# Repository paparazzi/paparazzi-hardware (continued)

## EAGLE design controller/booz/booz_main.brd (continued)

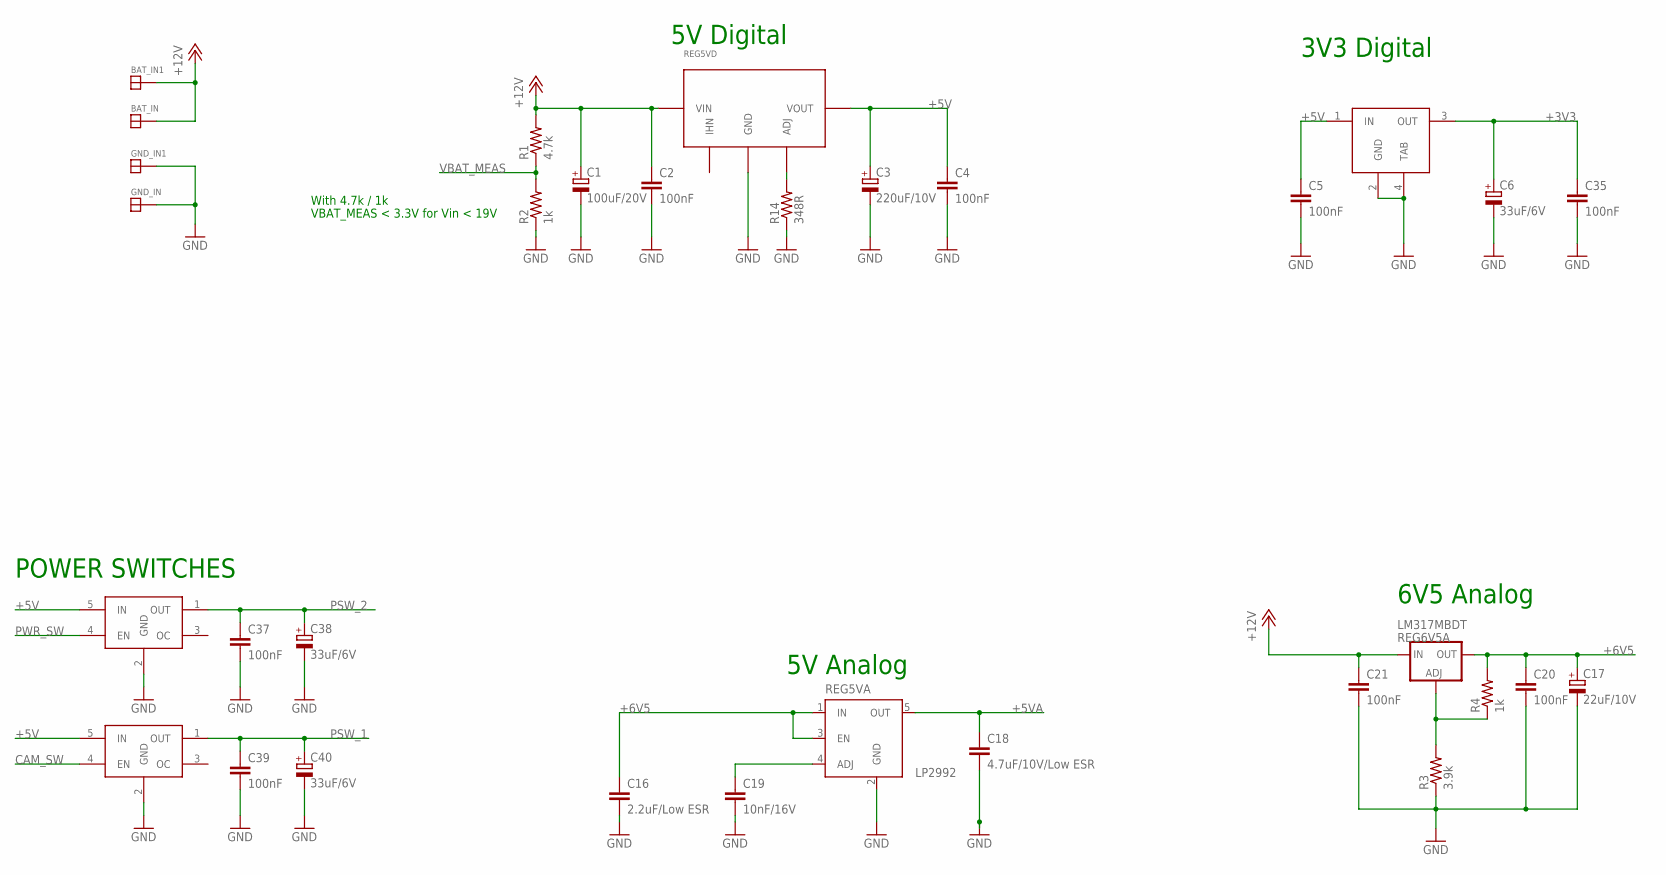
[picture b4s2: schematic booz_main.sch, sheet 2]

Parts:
BAT_IN, BAT_IN1: SOLDER_PAD150_75; SOLD_PAD_150_75
C1: 100uF/20V; SMC_D
C2, C4, C5, C20, C21, C35, C37, C39: 100nF; C0603
C3: 220uF/10V; SMC_D
C6, C38, C40: 33uF/6V; CT3216
C16: 2.2uF/Low ESR; C0603
C17: 22uF/10V; CT3216
C18: 4.7uF/10V/Low ESR; C0805K
C19: 10nF/16V; C0603K
GND_IN, GND_IN1: SOLDER_PAD150_75; SOLD_PAD_150_75
R1: 4.7k; R0603
R2, R4: 1k; R0603
R3: 3.9k; R0603
R14: 348R; R0603
REG3V3D: LM3940IMP-3.3; SOT223-R
REG5VA: LP2992; SOT23-5
REG5VD: PTHTH; PTH_TH
REG6V5A: LM317MBDT; DPACK
U$12, U$13: TPS2051B; SOT23-5L

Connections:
+3V3: C6.+, C35.1, REG3V3D.3 (OUT); also elsewhere on the board
+5V: C3.+, C4.1, C5.1, REG3V3D.1 (IN), REG5VD.P$3 (VOUT), U$12.5 (IN), U$13.5 (IN); also elsewhere on the board
+5VA: C18.1, REG5VA.5 (OUT); also elsewhere on the board
+6V5: C16.1, C17.+, C20.1, R4.2, REG5VA.1 (IN), REG5VA.3 (EN), REG6V5A.4 (OUT); also elsewhere on the board
+12V: BAT_IN.P$1, BAT_IN1.P$1, C1.+, C2.1, C21.1, R1.2, REG5VD.P$1 (VIN), REG6V5A.3 (IN)
CAM_SW: U$13.4 (EN); also elsewhere on the board
GND: C1.-, C2.2, C3.-, C4.2, C5.2, C6.-, C16.2, C17.-, C18.2, C19.2, C20.2, C21.2, C35.2, C37.2, C38.-, C39.2, C40.-, GND_IN.P$1, GND_IN1.P$1, R2.1, R3.1, R14.1, REG3V3D.2 (GND), REG3V3D.4 (TAB), REG5VA.2 (GND), REG5VD.P$2 (GND), U$12.2 (GND), U$13.2 (GND); also elsewhere on the board
unnamed: R14.2, REG5VD.P$4 (ADJ)
unnamed: C19.1, REG5VA.4 (ADJ)
unnamed: R3.2, R4.1, REG6V5A.1 (ADJ)
PSW_1: C39.1, C40.+, U$13.1 (OUT); also elsewhere on the board
PSW_2: C37.1, C38.+, U$12.1 (OUT); also elsewhere on the board
PWR_SW: U$12.4 (EN); also elsewhere on the board
VBAT_MEAS: R1.1, R2.2; also elsewhere on the board

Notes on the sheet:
5V Digital
3V3 Digital
6V5 Analog
5V Analog
POWER SWITCHES
With 4.7k / 1k
VBAT_MEAS < 3.3V for Vin < 19V

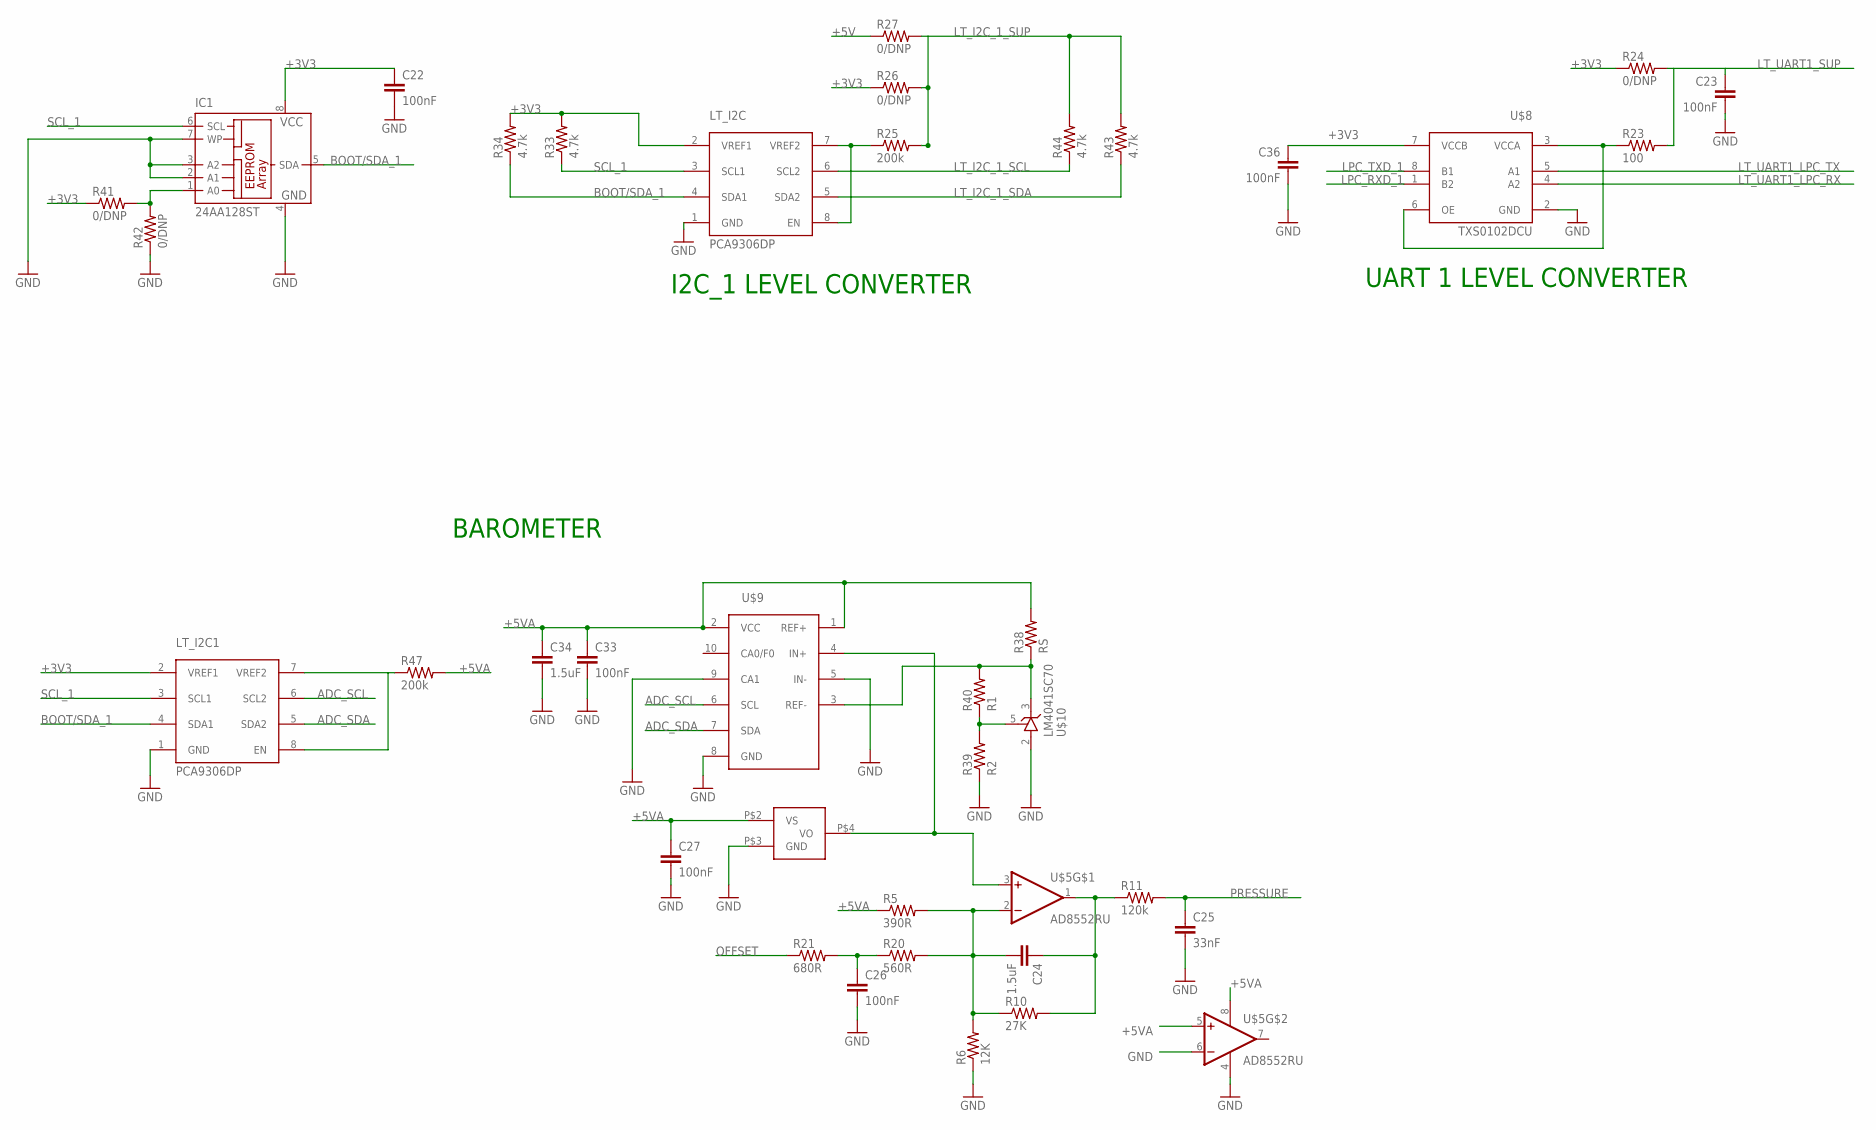
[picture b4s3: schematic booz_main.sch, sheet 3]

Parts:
C22, C23, C26, C27, C33, C36: 100nF; C0603
C24, C34: 1.5uF; C0805
C25: 33nF; C0805K
IC1: 24AA128ST; TSSOP8
LT_I2C, LT_I2C1: PCA9306DP; TSSOP_B3
R5: 390R; R0603
R6: 12K; R0603
R10: 27K; R0603
R11: 120k; R0603
R20: 560R; R0603
R21: 680R; R0603
R23: 100; R0603
R24, R26, R27, R41, R42: 0/DNP; R0603
R25, R47: 200k; R0603
R33, R34, R43, R44: 4.7k; R0603
R38: RS; R0603
R39: R2; R0603
R40: R1; R0603
U$2: MPX6115; CASE_1317
U$5: AD8552RU; TSSOP8
U$8: TXS0102DCU; US8
U$9: LTC2485; DFN10
U$10: LM4041SC70; SC70-5L

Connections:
+3V3: C22.1, C36.1, IC1.8 (VCC), LT_I2C.2 (VREF1), LT_I2C1.2 (VREF1), R24.1, R26.1, R33.2, R34.2, R41.1, U$8.7 (VCCB); also elsewhere on the board
+5V: R27.1; also elsewhere on the board
+5VA: C27.1, C33.1, C34.1, R5.1, R38.2, R47.2, U$2.P$2 (VS), U$5.5 (+IN), U$5.8 (V+), U$9.1 (REF+), U$9.2 (VCC); also elsewhere on the board
ADC_SCL: LT_I2C1.6 (SCL2), U$9.6 (SCL)
ADC_SDA: LT_I2C1.5 (SDA2), U$9.7 (SDA)
BOOT/SDA_1: IC1.5 (SDA), LT_I2C.4 (SDA1), LT_I2C1.4 (SDA1), R34.1; also elsewhere on the board
GND: C22.2, C23.2, C25.2, C26.2, C27.2, C33.2, C34.2, C36.2, IC1.2 (A1), IC1.3 (A2), IC1.4 (GND), IC1.7 (WP), LT_I2C.1 (GND), LT_I2C1.1 (GND), R6.1, R39.1, R42.1, U$2.P$3 (GND), U$5.4 (V-), U$5.6 (-IN), U$8.2 (GND), U$9.5 (IN-), U$9.8 (GND), U$9.9 (CA1), U$10.2 (A); also elsewhere on the board
LPC_RXD_1: U$8.1 (B2); also elsewhere on the board
LPC_TXD_1: U$8.8 (B1); also elsewhere on the board
LT_I2C_1_SCL: LT_I2C.6 (SCL2), R44.1; also elsewhere on the board
LT_I2C_1_SDA: LT_I2C.5 (SDA2), R43.1; also elsewhere on the board
LT_I2C_1_SUP: R25.2, R26.2, R27.2, R43.2, R44.2; also elsewhere on the board
LT_UART1_LPC_RX: U$8.4 (A2); also elsewhere on the board
LT_UART1_LPC_TX: U$8.5 (A1); also elsewhere on the board
LT_UART1_SUP: C23.1, R23.2, R24.2; also elsewhere on the board
unnamed: C24.2, R5.2, R6.2, R10.1, R20.2, U$5.2 (-IN)
unnamed: C24.1, R10.2, R11.1, U$5.1 (OUT)
unnamed: C26.1, R20.1, R21.2
unnamed: R23.1, U$8.3 (VCCA), U$8.6 (OE)
unnamed: R39.2, R40.1, U$10.5 (R)
unnamed: LT_I2C.7 (VREF2), LT_I2C.8 (EN), R25.1
unnamed: IC1.1 (A0), R41.2, R42.2
unnamed: LT_I2C1.7 (VREF2), LT_I2C1.8 (EN), R47.1
unnamed: R38.1, R40.2, U$9.3 (REF-), U$10.3 (C)
OFFSET: R21.1; also elsewhere on the board
PRESSURE: C25.1, R11.2; also elsewhere on the board
PRESSURE_RAW: U$2.P$4 (VO), U$5.3 (+IN), U$9.4 (IN+)
SCL_1: IC1.6 (SCL), LT_I2C.3 (SCL1), LT_I2C1.3 (SCL1), R33.1; also elsewhere on the board

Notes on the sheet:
I2C_1 LEVEL CONVERTER
UART 1 LEVEL CONVERTER
BAROMETER

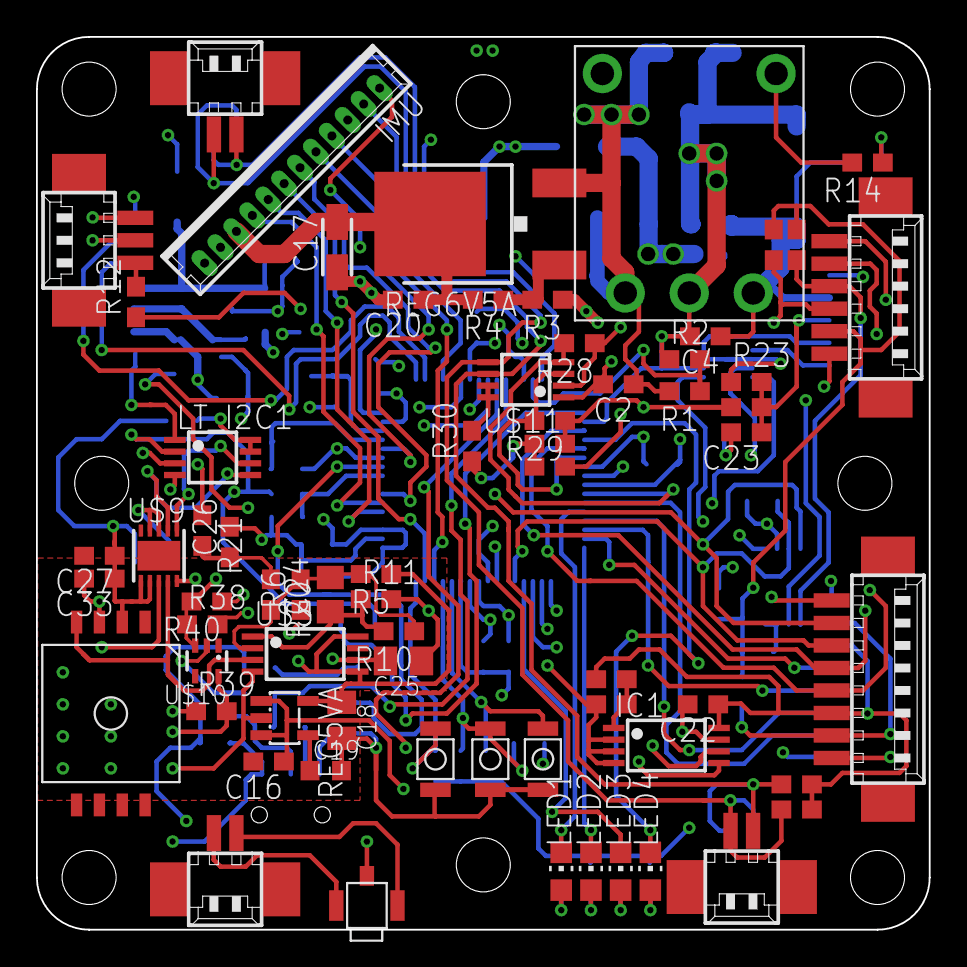
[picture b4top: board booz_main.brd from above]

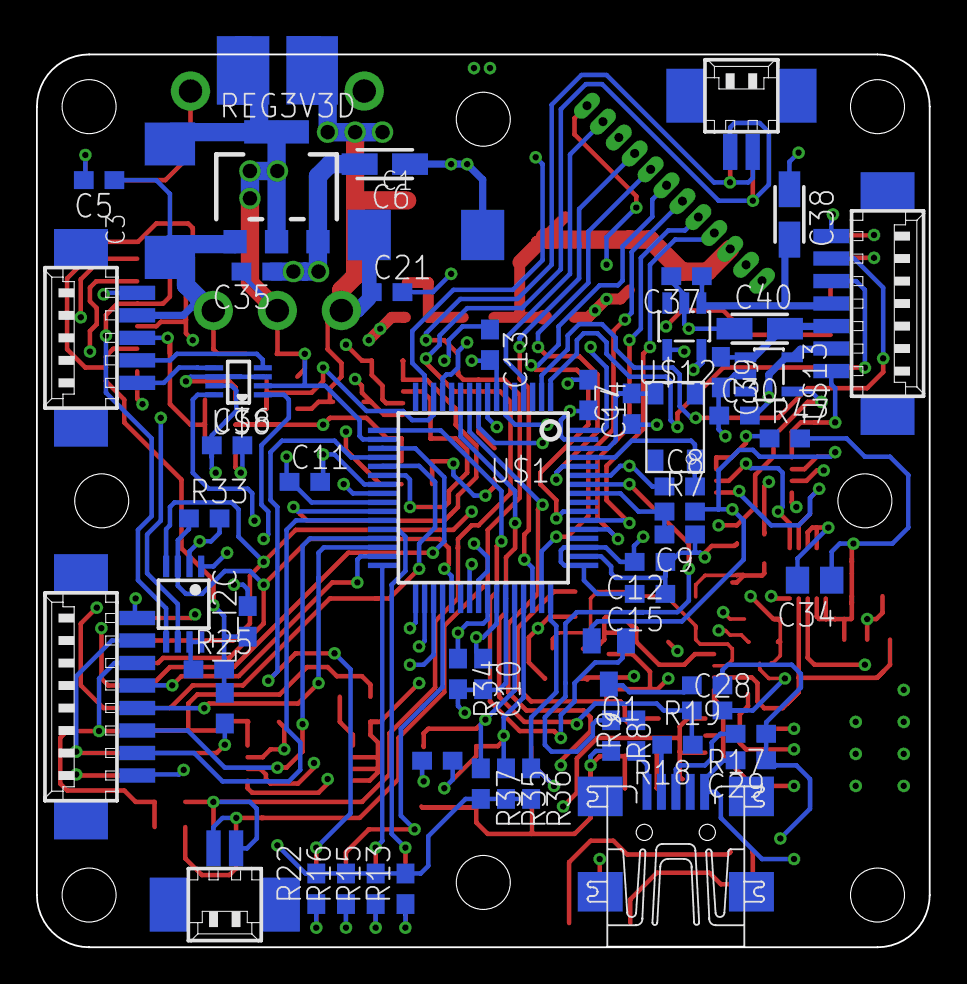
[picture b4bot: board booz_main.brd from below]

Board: 4 copper layers, 49.6 x 49.6 mm, 129 parts (62 on the bottom side), 90 nets.

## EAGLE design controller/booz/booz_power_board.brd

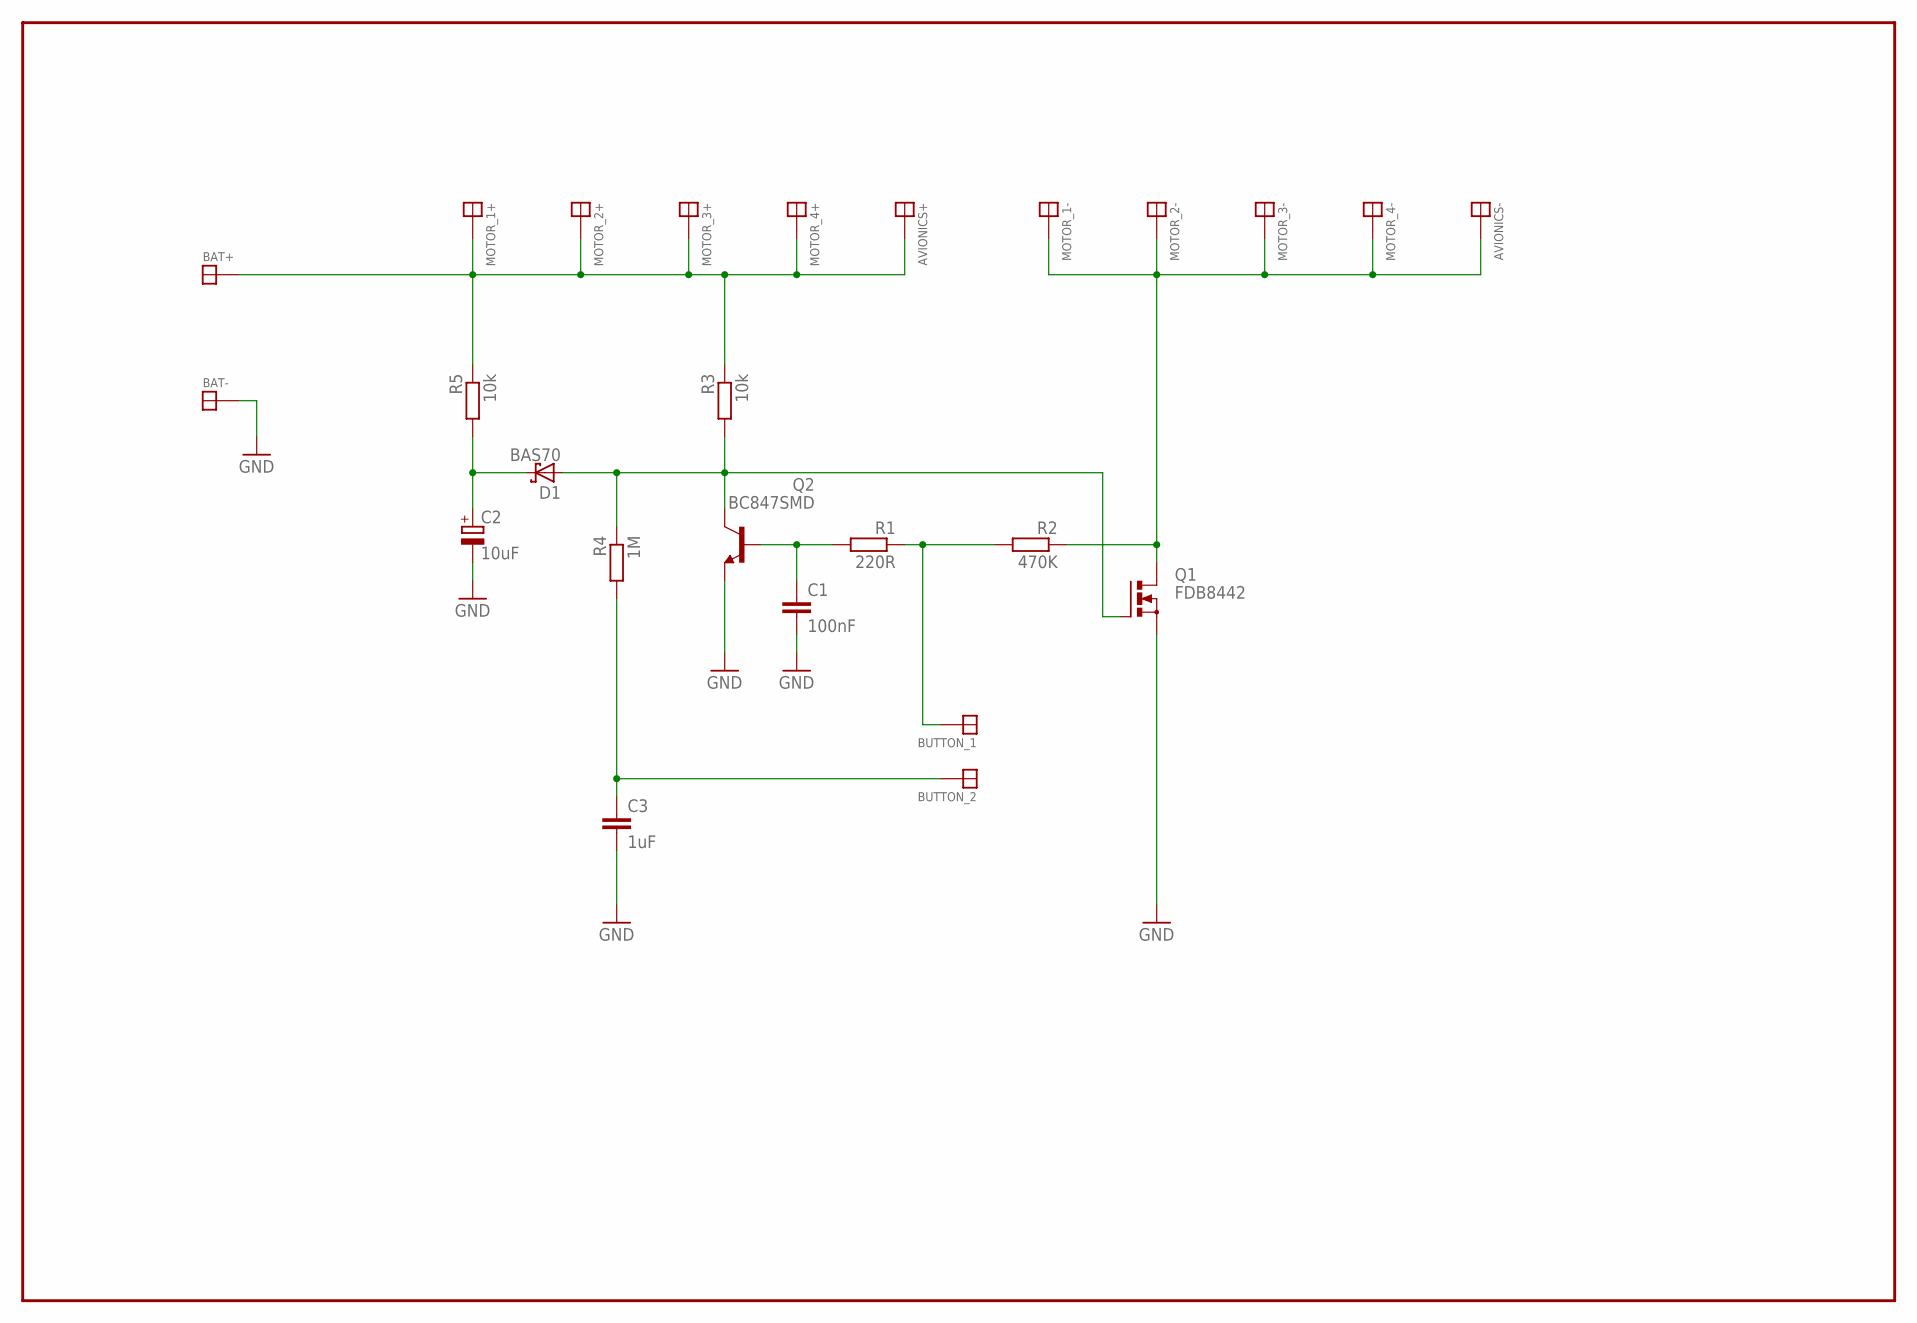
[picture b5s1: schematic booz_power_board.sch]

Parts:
AVIONICS+: SOLDER_PAD100_50; SOLDER_PAD_100_50
AVIONICS-: SOLDER_PAD100_50; SOLDER_PAD_100_50
BAT+: SOLDER_PAD100_50; SOLDER_PAD_100_50
BAT-: SOLDER_PAD100_50; SOLDER_PAD_100_50
BUTTON_1, BUTTON_2: SOLDER_PAD100_50; SOLDER_PAD_100_50
C1: 100nF; C0603
C2: 10uF; SMC_A
C3: 1uF; C0603
D1: BAS70; SOT23
MOTOR_1+, MOTOR_1-, MOTOR_2+, MOTOR_2-, MOTOR_3+, MOTOR_3-, MOTOR_4+, MOTOR_4-: SOLDER_PAD100_50; SOLDER_PAD_100_50
Q1: FDB8442; TO263
Q2: BC847SMD; SOT23
R1: 220R; R1206
R2: 470K; R0603
R3: 10k; R1206
R4: 1M; R0603
R5: 10k; R0603

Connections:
GND: BAT-.P$1, C1.2, C2.-, C3.2, Q1.2 (S), Q2.2 (E)
unnamed: AVIONICS+.P$1, BAT+.P$1, MOTOR_1+.P$1, MOTOR_2+.P$1, MOTOR_3+.P$1, MOTOR_4+.P$1, R3.1, R5.1
unnamed: C1.1, Q2.1 (B), R1.2
unnamed: BUTTON_1.P$1, R1.1, R2.2
unnamed: BUTTON_2.P$1, C3.1, R4.2
unnamed: AVIONICS-.P$1, MOTOR_1-.P$1, MOTOR_2-.P$1, MOTOR_3-.P$1, MOTOR_4-.P$1, Q1.3 (D), R2.1
unnamed: D1.1 (A), Q1.1 (G), Q2.3 (C), R3.2, R4.1
unnamed: C2.+, D1.3 (C), R5.2

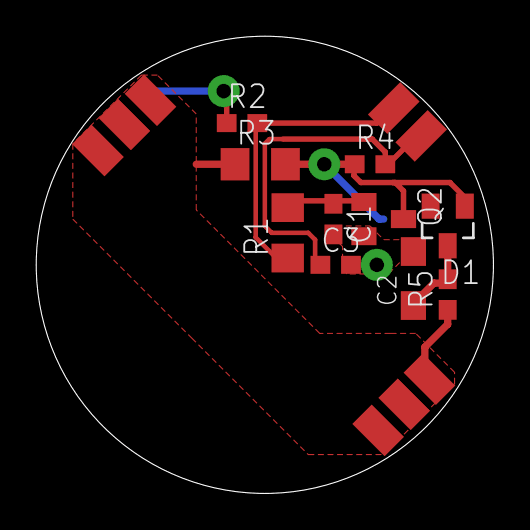
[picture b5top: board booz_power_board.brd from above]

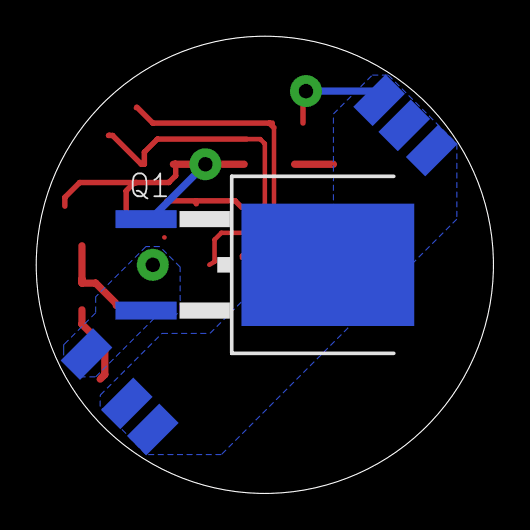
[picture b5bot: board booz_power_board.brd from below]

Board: 2 copper layers, 25.4 x 25.4 mm, 25 parts (7 on the bottom side), 8 nets.
